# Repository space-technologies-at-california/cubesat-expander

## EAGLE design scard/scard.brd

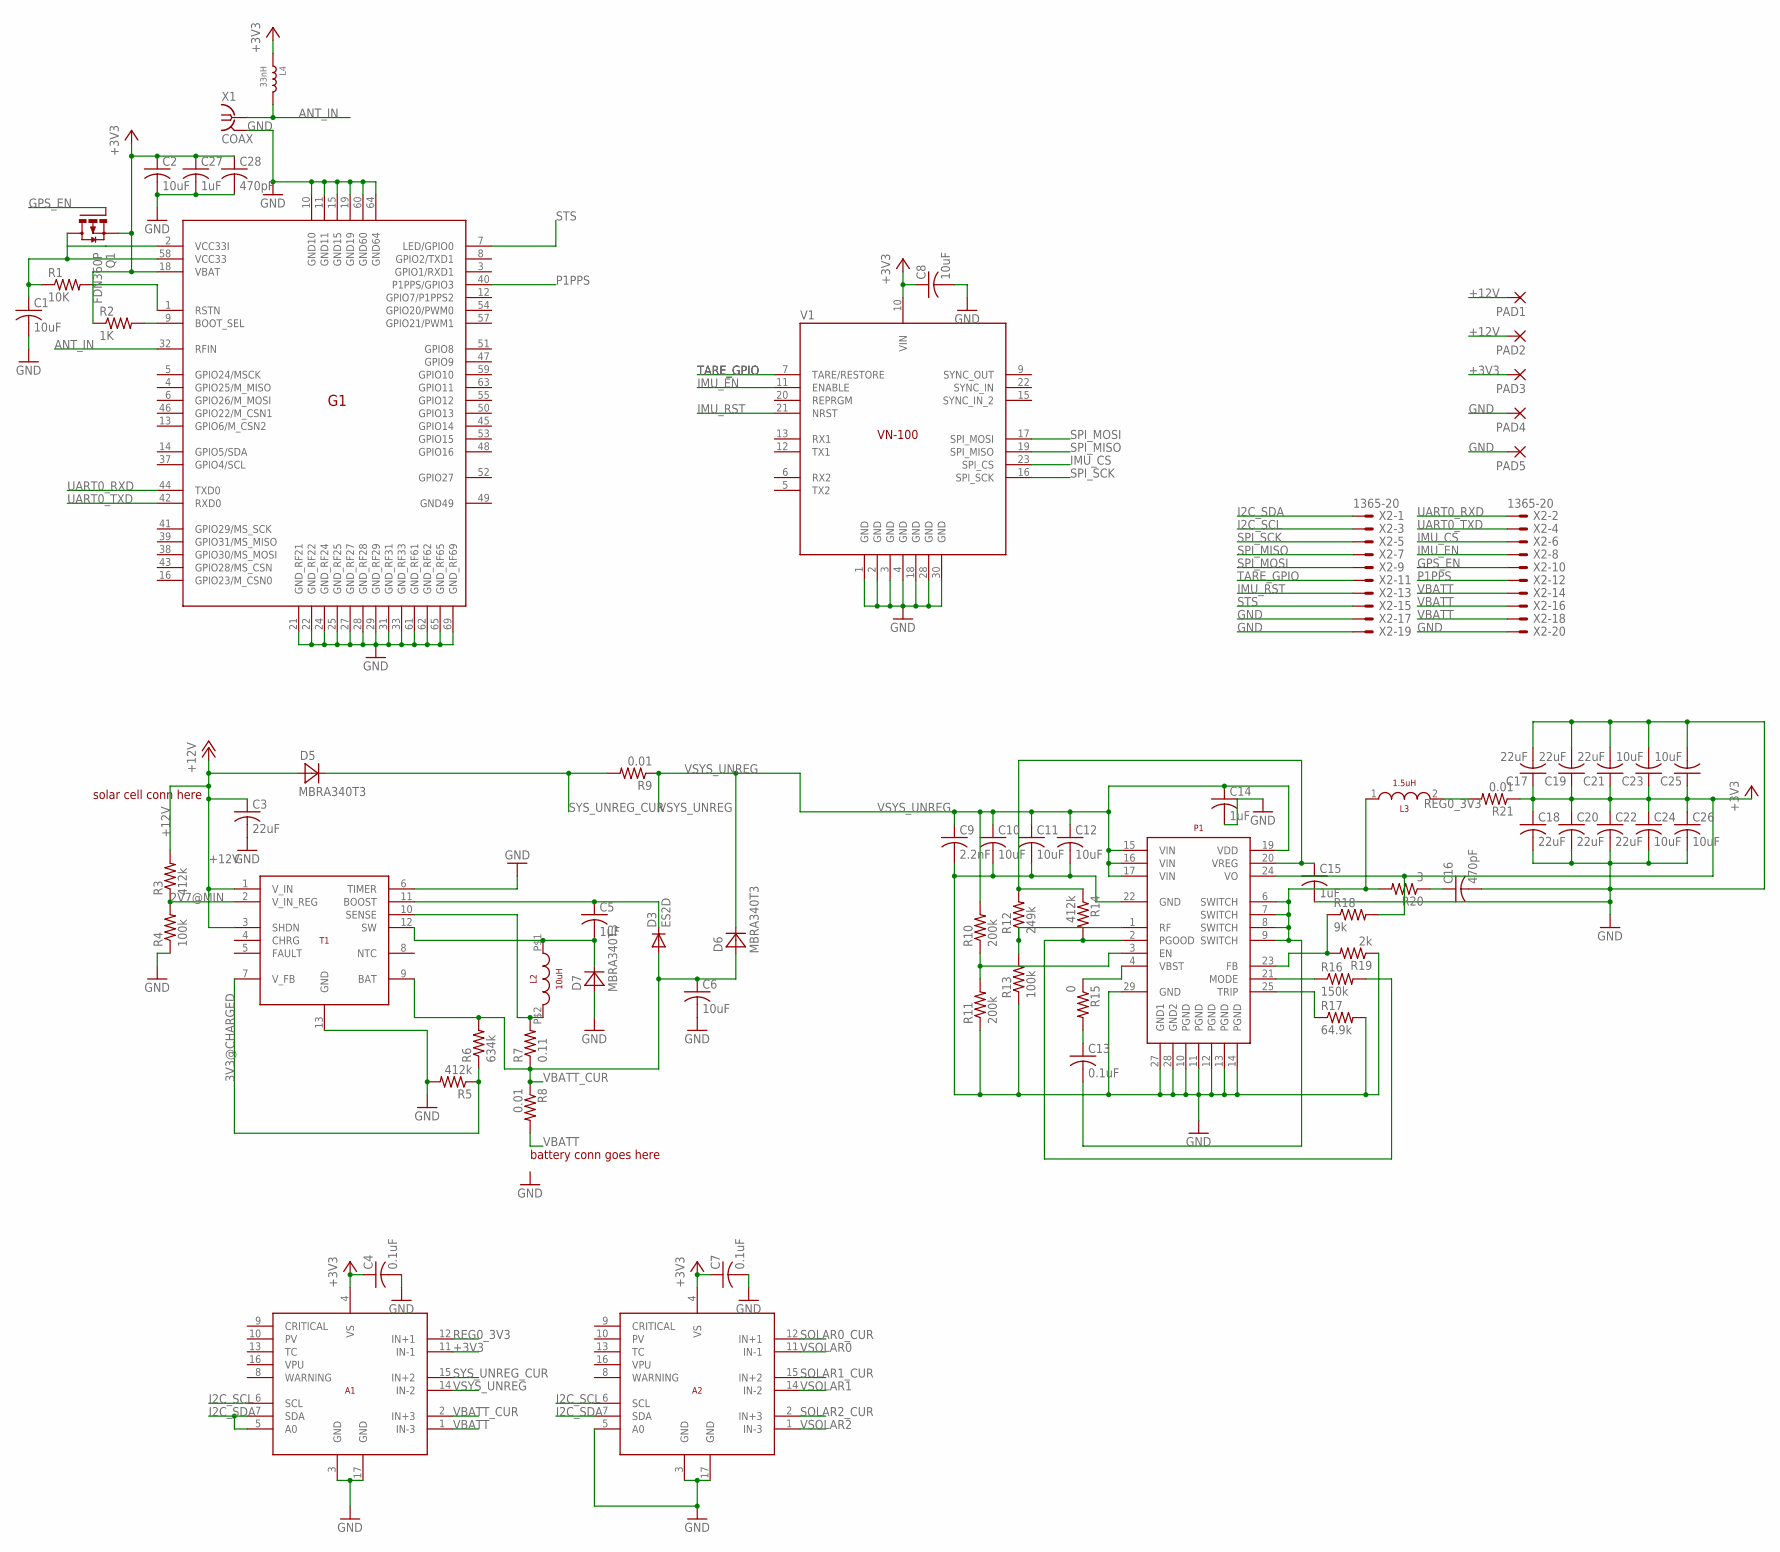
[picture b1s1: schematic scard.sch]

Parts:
A1, A2: INA3221-Q1; VQFN16
C1, C2, C8, C10, C11, C12, C23, C24, C25, C26: 10uF; C0603
C3, C17, C18, C19, C20, C21, C22: 22uF; C0805
C4, C7: 0.1uF; C0603
C5, C14, C15, C27: 1uF; C0402
C6: 10uF; C0805
C9: 2.2nF; C0402
C13: 0.1uF; C0402
C16, C28: 470pF; C0402
D3: ES2D; SMB
D5, D6, D7: MBRA340T3; SMA
G1: VENUS838FLPX-L; LGA69
L2: 10uH; SRP7030
L3: 1.5uH; SRP7028A
L4: 33nH; L0805
P1: TPS548A20; R-PWQFN-N28
PAD1, PAD2, PAD3, PAD4, PAD5: SMD5; SMD2,54-5,08
Q1: FDN360P; SUPER-SOT3
R1: 10K; R0603
R2: 1K; R0603
R3, R5, R14: 412k; R0603
R4, R13: 100k; R0603
R6: 634k; R0603
R7: 0.11; R0603
R8, R9, R21: 0.01; R0603
R10, R11: 200k; R0603
R12: 249k; R0603
R15: 0; R0603
R16: 150k; R0603
R17: 64.9k; R0603
R18: 9k; R0603
R19: 2k; R0603
R20: 3; R0603
T1: LT3652; MSOP12
V1: VN100NORMAL; 7X8CASTLE
X1: COAX; MMCX-J-P-X-ST-EM1-MKT
X2: 1365-20

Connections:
2V7@MIN: R3.1, R4.2, T1.2 (V_IN_REG)
3V3@CHARGED: R5.1, R6.1, T1.7 (V_FB)
+3V3: A1.4 (VS), A1.11 (IN-1), A2.4 (VS), C2.1, C4.1, C7.1, C8.1, C17.1, C18.1, C19.1, C20.1, C21.1, C22.1, C23.1, C24.1, C25.1, C26.1, C27.1, C28.1, G1.18 (VBAT), L4.1, P1.24 (VO), PAD3.1, Q1.2 (S), R2.1, R18.2, R21.1, V1.10 (VIN)
+12V: C3.1, D5.A, PAD1.1, PAD2.1, R3.2, T1.1 (V_IN), T1.3 (SHDN)
ANT_IN: G1.32 (RFIN), L4.2, X1.1
GND: A1.3 (GND), A1.17 (GND), A2.3 (GND), A2.5 (A0), A2.17 (GND), C1.2, C2.2, C3.2, C4.2, C6.2, C7.2, C8.2, C9.2, C10.2, C11.2, C12.2, C14.2, C15.2, C16.2, C17.2, C18.2, C19.2, C20.2, C21.2, C22.2, C23.2, C24.2, C25.2, C26.2, C27.2, C28.2, D7.A, G1.10 (GND10), G1.11 (GND11), G1.15 (GND15), G1.19 (GND19), G1.21 (GND_RF21), G1.22 (GND_RF22), G1.24 (GND_RF24), G1.25 (GND_RF25), G1.27 (GND_RF27), G1.28 (GND_RF28), G1.29 (GND_RF29), G1.31 (GND_RF31), G1.33 (GND_RF33), G1.60 (GND60), G1.61 (GND_RF61), G1.62 (GND_RF62), G1.64 (GND64), G1.65 (GND_RF65), G1.69 (GND_RF69), P1.10 (PGND), P1.11 (PGND), P1.12 (PGND), P1.13 (PGND), P1.14 (PGND), P1.22 (GND), P1.27 (GND1), P1.28 (GND2), P1.29 (GND), PAD4.1, PAD5.1, R4.1, R5.2, R11.1, R13.1, R17.2, R19.1, T1.6 (TIMER), T1.13 (GND), V1.1 (GND), V1.2 (GND), V1.3 (GND), V1.4 (GND), V1.18 (GND), V1.28 (GND), V1.30 (GND), X1.2@1 (GND), X1.2@2 (GND), X1.2@3 (GND), X1.2@4 (GND), X2.17, X2.19, X2.20
GPS_EN: Q1.1 (G), X2.10
I2C_SCL: A1.6 (SCL), A2.6 (SCL), X2.3
I2C_SDA: A1.5 (A0), A1.7 (SDA), A2.7 (SDA), X2.1
IMU_CS: V1.23 (SPI_CS), X2.6
IMU_EN: V1.11 (ENABLE), X2.8
IMU_RST: V1.21 (NRST), X2.13
unnamed: P1.21 (MODE), R16.1
unnamed: C13.2, L3.1, P1.6 (SWITCH), P1.7 (SWITCH), P1.8 (SWITCH), P1.9 (SWITCH), R20.2
unnamed: C5.1, D3.C, T1.11 (BOOST)
unnamed: P1.4 (VBST), R15.1
unnamed: L2.P$2, R7.2, T1.10 (SENSE)
unnamed: G1.9 (BOOT_SEL), R2.2
unnamed: G1.1 (RSTN), R1.2
unnamed: C13.1, R15.2
unnamed: C15.1, P1.20 (VREG), R12.2, R14.1
unnamed: P1.1 (RF), R12.1, R13.2
unnamed: P1.2 (PGOOD), R14.2, R16.2
unnamed: P1.25 (TRIP), R17.1
unnamed: P1.23 (FB), R18.1, R19.2
unnamed: P1.3 (EN), R10.1, R11.2
unnamed: C1.1, G1.2 (VCC33I), G1.58 (VCC33), Q1.3 (D), R1.1
unnamed: C16.1, R20.1
unnamed: C5.2, D7.C, L2.P$1, T1.12 (SW)
P1PPS: G1.40 (P1PPS/GPIO3), X2.12
REG0_3V3: A1.12 (IN+1), L3.2, R21.2
SOLAR0_CUR: A2.12 (IN+1)
SOLAR1_CUR: A2.15 (IN+2)
SOLAR2_CUR: A2.2 (IN+3)
SPI_MISO: V1.19 (SPI_MISO), X2.7
SPI_MOSI: V1.17 (SPI_MOSI), X2.9
SPI_SCK: V1.16 (SPI_SCK), X2.5
STS: G1.7 (LED/GPIO0), X2.15
SYS_UNREG_CUR: A1.15 (IN+2), D5.C, R9.2
TARE_GPIO: V1.7 (TARE/RESTORE), X2.11
UART0_RXD: G1.44 (TXD0), X2.2
UART0_TXD: G1.42 (RXD0), X2.4
VBATT: A1.1 (IN-3), R8.2, X2.14, X2.16, X2.18
VBATT_CUR: A1.2 (IN+3), C6.1, D3.A, D6.A, R6.2, R7.1, R8.1, T1.9 (BAT)
VSOLAR0: A2.11 (IN-1)
VSOLAR1: A2.14 (IN-2)
VSOLAR2: A2.1 (IN-3)
VSYS_UNREG: A1.14 (IN-2), C9.1, C10.1, C11.1, C12.1, C14.1, D6.C, P1.15 (VIN), P1.16 (VIN), P1.17 (VIN), P1.19 (VDD), R9.1, R10.2

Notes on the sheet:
battery conn goes here
solar cell conn here

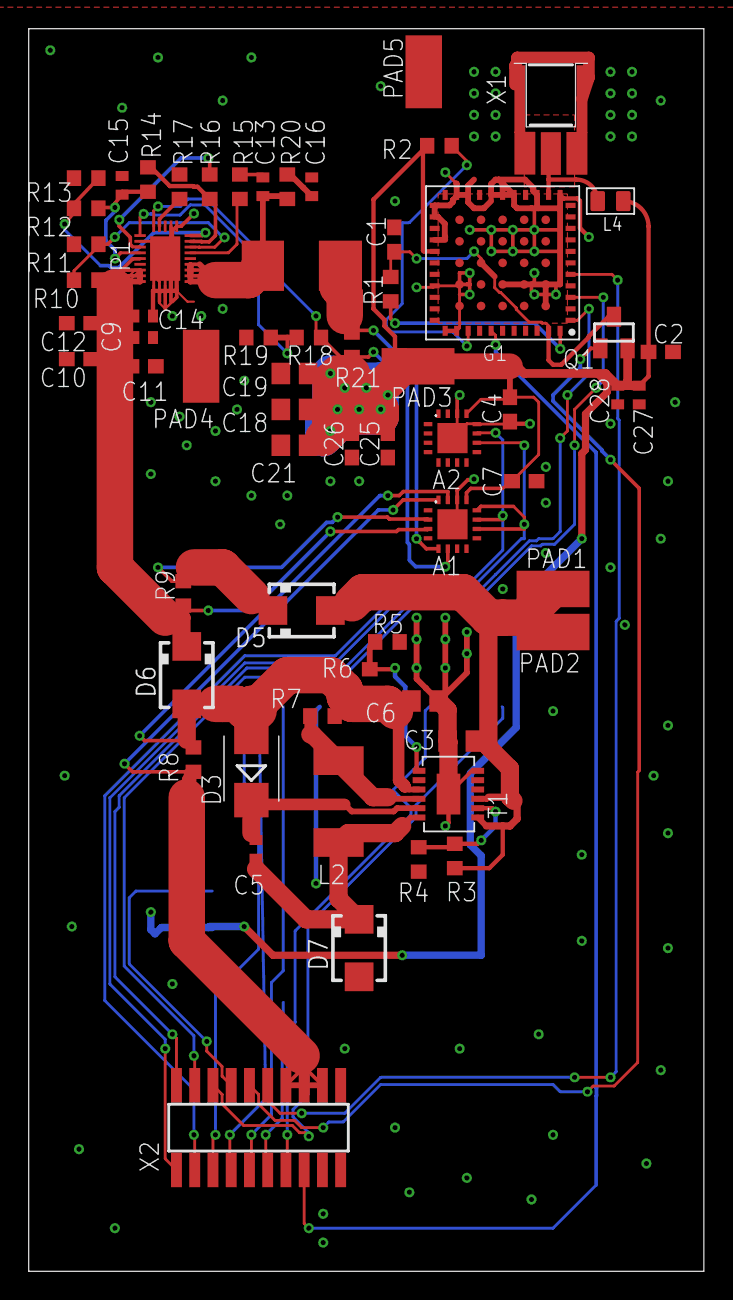
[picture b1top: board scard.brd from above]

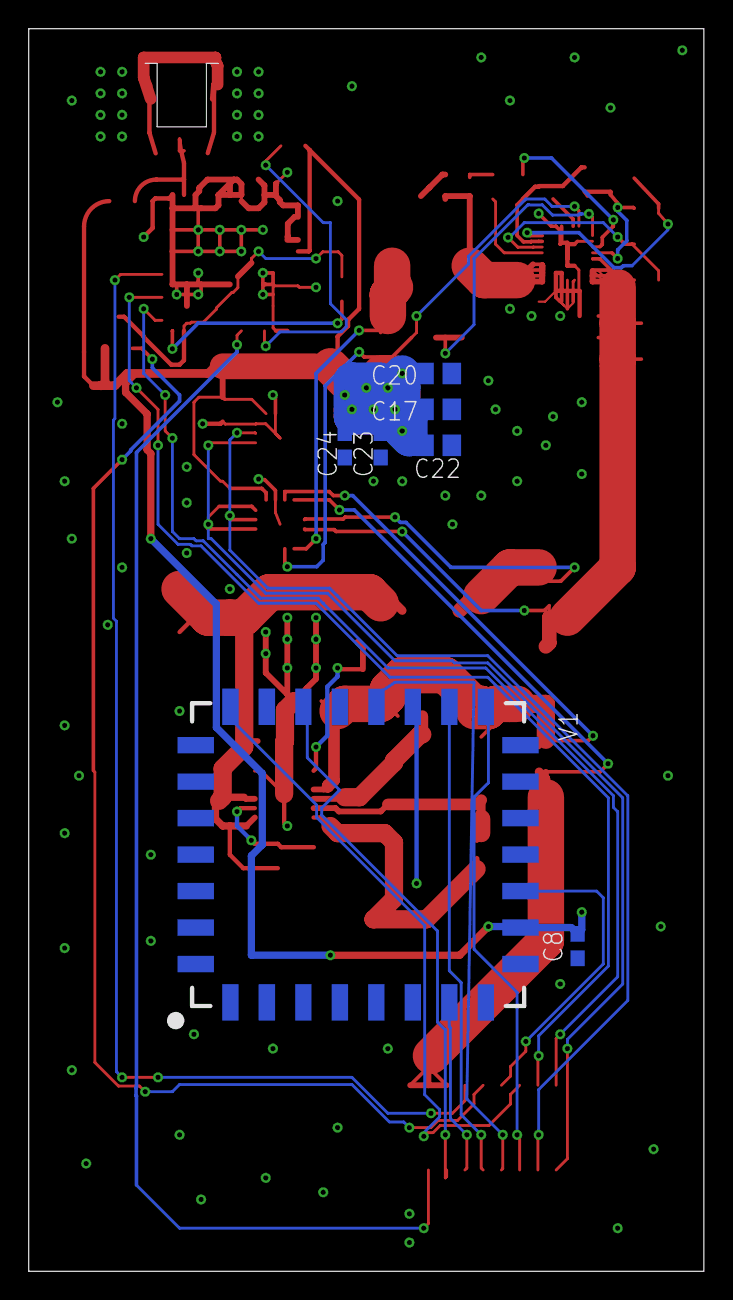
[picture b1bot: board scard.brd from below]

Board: 2 copper layers, 47.0 x 86.5 mm, 70 parts (7 on the bottom side), 42 nets.

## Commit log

2017-09-29 initial with GPS, IMU, and antenna conn
2017-09-29 better makefile
2017-09-30 added battery charging IC to library
2017-09-30 BQ24773 application circuit added
2017-10-01 nearly completed charging IC circuit and switching regulators
2017-10-01 tentatively completed battery charging IC supporting circuitry
2017-10-01 fixed sense resistor placement for charger
2017-10-02 finished adding tps63070 switching regulator
2017-10-03 added inductor part and completed schematic for 3v3 voltage regulators
2017-10-03 added voltage and current telemetry to battery and 3v3 regulators via an 8 channel adc
2017-10-03 upgraded eagle version
2017-10-04 removed unnecessary autosave files
2017-10-05 first stage of layout for power systems
2017-10-07 finished test board v0.1 layout and added pictures
2017-10-07 added solder mask over vias
2017-10-07 shrunk size to save money
2017-10-09 changes from design review
2017-10-10 fixed ground plane on GPS
2017-10-13 need switching voltage regulator capable of up to 8A
2017-10-23 Andrea's changes, including routing power supply components, gps thermal vias, and more capacitors
2017-10-23 final DRC fixes
2017-10-23 CAM files added
2017-10-24 fixed misplaced current measurement traces at Brent's suggestion
2017-10-25 added new 10uH inductor due to original inductor going out of stock. Updated CAM files. Fixed issue with GPS pads having no thermals
2017-10-27 better power traces for voltage regulator
2017-10-28 Started v0.4 S Card moved gps far from power inductor reorganized battery charging circuit in preparation for routing
2017-10-31 Added solder stencil gerber files
2017-11-10 moved silkscreen labels and generated assembly files including drawings and pick and place files
